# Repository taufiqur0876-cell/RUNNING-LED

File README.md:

# Running LED (RUNNING_LED_FF)

Proyek PCB **running LED** (lampu LED berjalan) yang dirancang di **KiCad**. Sinyal clock dihasilkan oleh timer **NE555** (mode astable) lalu diteruskan ke counter **CD4017** untuk menggeser nyala LED satu per satu.

## Status

🚧 Prototipe — desain skematik dan layout PCB sudah dibuat, tahap pengujian dan debugging rangkaian.

## Cara Kerja Singkat

1. **Regulator tegangan** (LD1117S50) menurunkan tegangan masukan (VIN) menjadi VCC 5 V untuk seluruh rangkaian.
2. **NE555** bekerja sebagai osilator astable. Frekuensinya ditentukan oleh resistor, dioda 1N4148, dan kapasitor C6 pada jalur DIS/THR/TR. Keluarannya (`555_OUT`) menjadi sinyal clock.
3. **CD4017** menerima clock di pin CLK, lalu menggeser keluaran aktif (Q0 ... Q9) satu langkah setiap pulsa sehingga LED menyala bergantian.
4. **LED indikator** menunjukkan kondisi catu daya dan keluaran 555.
5. Terdapat juga rangkaian **astable multivibrator** dari dua transistor MMBT3904 dengan dua LED yang berkedip bergantian.

## Komponen Utama

| Komponen | Fungsi |
|---|---|
| LD1117S50 | Regulator tegangan 5 V |
| NE555 | Pembangkit clock (astable) |
| CD4017 | Counter dekade, penggeser LED |
| MMBT3904 (x2) | Astable multivibrator transistor |
| 1N4148 (x2) | Pengatur siklus kerja (duty cycle) 555 |
| LED + resistor 220 ohm | Indikator dan LED berjalan |

## Gambar

### Skematik

### Layout PCB

## Struktur Repositori

```
.
├── README.md
├── images/
│   ├── schematic.png
│   └── pcb-layout.png
└── RUNNING_LED_FF.kicad_pcb   # file desain KiCad
```

## Cara Membuka

1. Pasang [KiCad](https://www.kicad.org/).
2. Buka file proyek (`.kicad_pro`) atau langsung `RUNNING_LED_FF.kicad_pcb`.

## Penulis

Taufiqur Rahman — Politeknik Elektronika Negeri Surabaya (PENS)

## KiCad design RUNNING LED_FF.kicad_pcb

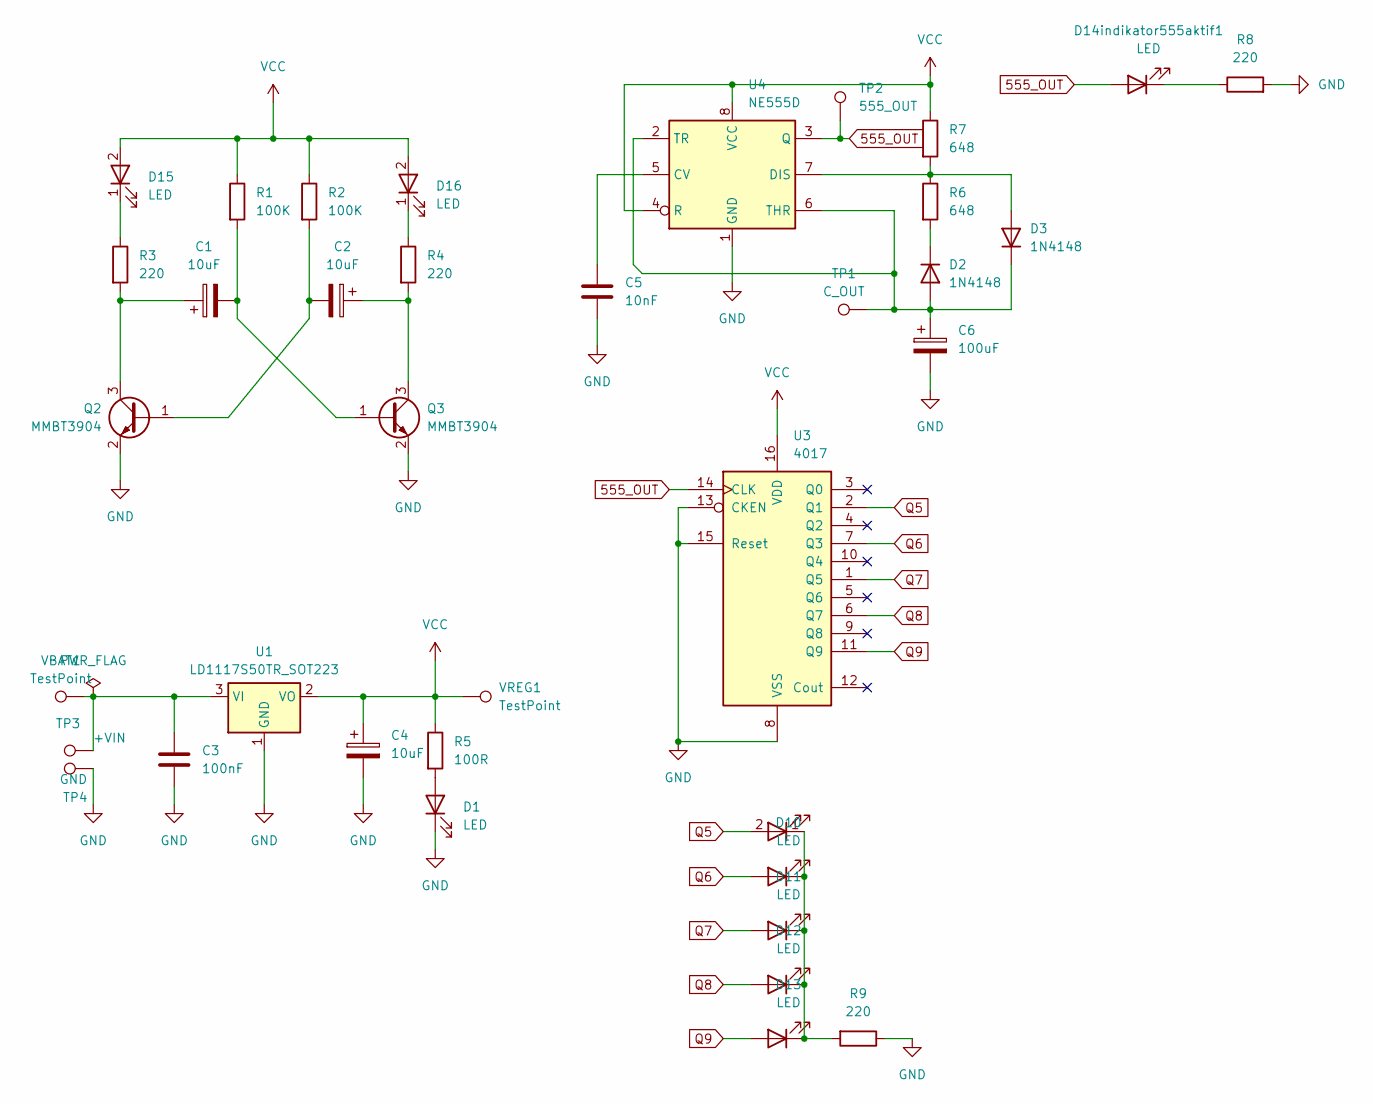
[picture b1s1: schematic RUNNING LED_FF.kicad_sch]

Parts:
C1, C2, C4: 10uF; C_Elec_6.3x5.4
C3: 100nF; C_0805_2012Metric
C5: 10nF; C_0805_2012Metric
C6: 100uF; C_Elec_6.3x5.4
D1, D9, D10, D11, D13, D14indikator555aktif1, D15, D16: LED; LED_1206_3216Metric
D2, D3: 1N4148; D_MiniMELF
D12: LED; LED_1206_3216Metric_Pad1.42x1.75mm_HandSolder
Q2, Q3: MMBT3904; SOT-23
R1, R2: 100K; R_0805_2012Metric
R3, R4, R8, R9: 220; R_0805_2012Metric
R5: 100R; R_0805_2012Metric
R6, R7: 648; R_0805_2012Metric
TP1: C_OUT; TestPoint_Pad_D3.0mm
TP2: 555_OUT; TestPoint_Pad_D3.0mm
TP3: +VIN; TestPoint_Pad_2.5x2.5mm
TP4: GND; TestPoint_Pad_2.5x2.5mm
U1: LD1117S50TR_SOT223; SOT-223
U3: 4017; SOIC-16_3.9x9.9mm_P1.27mm
U4: NE555D; SO-8_3.9x4.9mm_P1.27mm
VBAT1: TestPoint; TestPoint_Pad_D3.0mm
VREG1: TestPoint; TestPoint_Pad_D3.0mm

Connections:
555_OUT: D14indikator555aktif1.2 (A), TP2.1, U3.14 (CLK), U4.3 (Q)
GND: C3.2, C4.2, C5.2, C6.2, D1.1 (K), Q2.2 (E), Q3.2 (E), R8.2, R9.1, TP4.1, U1.1 (GND), U3.8 (VSS), U3.13 (CKEN), U3.15 (Reset), U4.1 (GND)
unnamed: D1.2 (A), R5.2
unnamed: C6.1, D2.2 (A), D3.1 (K), TP1.1, U4.2 (TR), U4.6 (THR)
unnamed: D2.1 (K), R6.2
unnamed: D3.2 (A), R6.1, R7.2, U4.7 (DIS)
unnamed: D9.1 (K), D10.1 (K), D11.1 (K), D12.1 (K), D13.1 (K), R9.2
unnamed: D14indikator555aktif1.1 (K), R8.1
unnamed: D15.1 (K), R3.1
unnamed: D16.1 (K), R4.1
unnamed: C2.2, Q2.1 (B), R2.2
unnamed: C1.1, Q2.3 (C), R3.2
unnamed: C1.2, Q3.1 (B), R1.2
unnamed: C2.1, Q3.3 (C), R4.2
unnamed: C3.1, TP3.1, U1.3 (VI), VBAT1.1
unnamed: C5.1, U4.5 (CV)
Q5: D9.2 (A), U3.2 (Q1)
Q6: D10.2 (A), U3.7 (Q3)
Q7: D11.2 (A), U3.1 (Q5)
Q8: D12.2 (A), U3.6 (Q7)
Q9: D13.2 (A), U3.11 (Q9)
VCC: C4.1, D15.2 (A), D16.2 (A), R1.1, R2.1, R5.1, R7.1, U1.2 (VO), U3.16 (VDD), U4.4 (R), U4.8 (VCC), VREG1.1

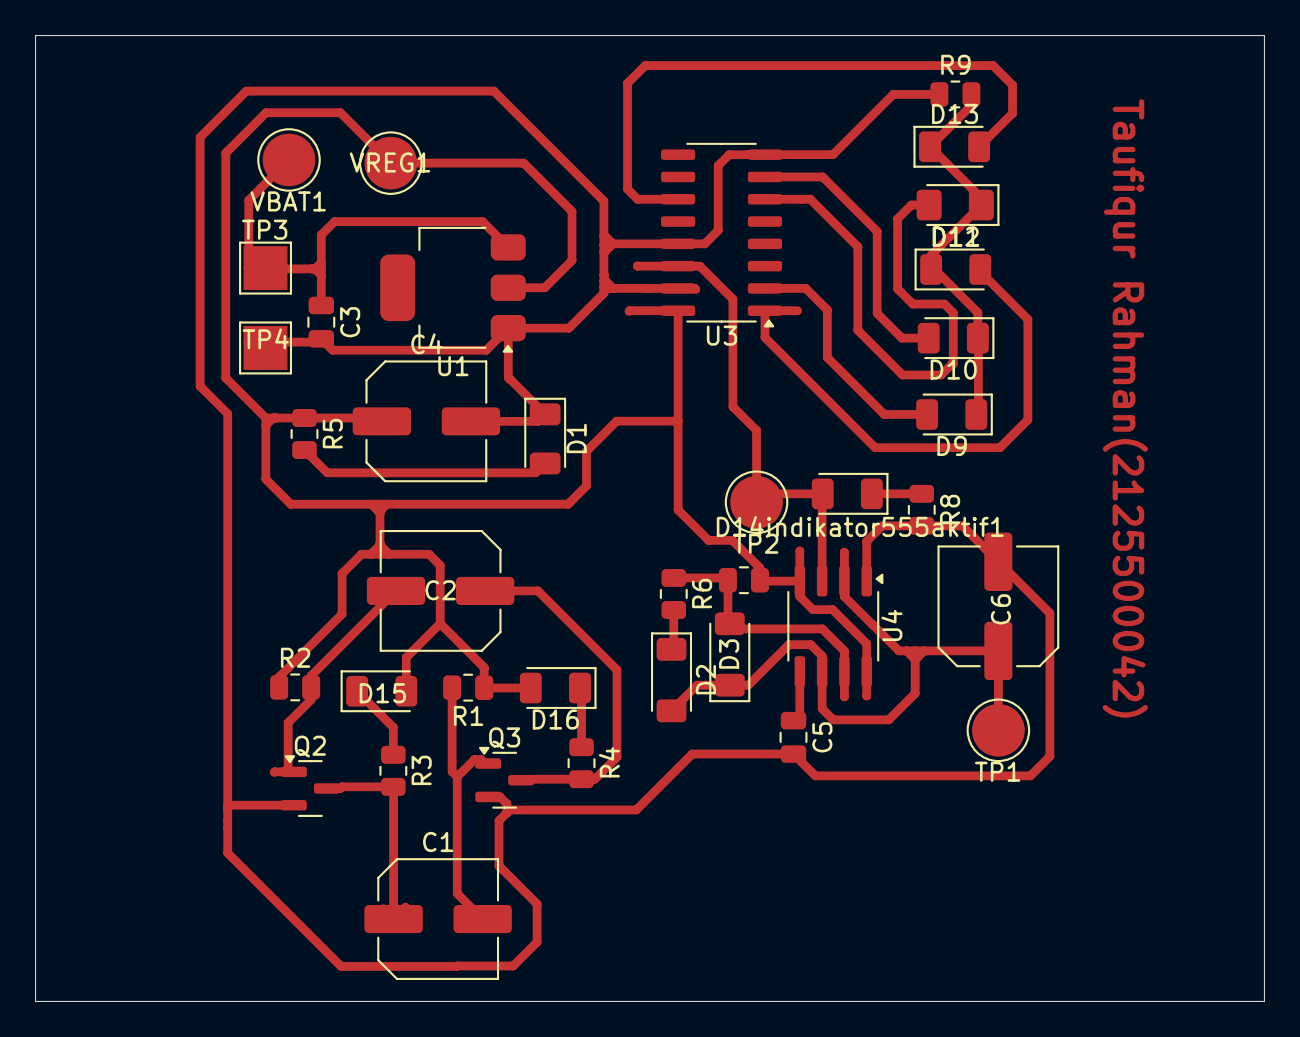
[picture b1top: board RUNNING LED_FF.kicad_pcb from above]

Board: 2 copper layers, 70.0 x 55.0 mm, 37 parts (0 on the bottom side), 22 nets.
